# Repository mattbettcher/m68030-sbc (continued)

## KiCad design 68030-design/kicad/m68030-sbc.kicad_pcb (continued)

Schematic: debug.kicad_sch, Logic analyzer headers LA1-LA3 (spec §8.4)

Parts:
J11: LA1 A31-A0; PinHeader_2x20_P2.54mm_Vertical; MPN Samtec TSW-120-07-G-D
J12: LA2 D31-D0; PinHeader_2x20_P2.54mm_Vertical; MPN Samtec TSW-120-07-G-D
J13: LA3 control; PinHeader_2x20_P2.54mm_Vertical; MPN Samtec TSW-120-07-G-D
TP1101: LED_n; TestPoint_Pad_D1.5mm
TP1102: HALT_LED_n; TestPoint_Pad_D1.5mm

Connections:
/A0: J11.39; also elsewhere on the board
/A1: J11.38; also elsewhere on the board
/A2: J11.37; also elsewhere on the board
/A3: J11.36; also elsewhere on the board
/A4: J11.34; also elsewhere on the board
/A5: J11.33; also elsewhere on the board
/A6: J11.32; also elsewhere on the board
/A7: J11.31; also elsewhere on the board
/A8: J11.29; also elsewhere on the board
/A9: J11.28; also elsewhere on the board
/A10: J11.27; also elsewhere on the board
/A11: J11.26; also elsewhere on the board
/A12: J11.24; also elsewhere on the board
/A13: J11.23; also elsewhere on the board
/A14: J11.22; also elsewhere on the board
/A15: J11.21; also elsewhere on the board
/A16: J11.19; also elsewhere on the board
/A17: J11.18; also elsewhere on the board
/A18: J11.17; also elsewhere on the board
/A19: J11.16; also elsewhere on the board
/A20: J11.14; also elsewhere on the board
/A21: J11.13; also elsewhere on the board
/A22: J11.12; also elsewhere on the board
/A23: J11.11; also elsewhere on the board
/A24: J11.9; also elsewhere on the board
/A25: J11.8; also elsewhere on the board
/A26: J11.7; also elsewhere on the board
/A27: J11.6; also elsewhere on the board
/A28: J11.4; also elsewhere on the board
/A29: J11.3; also elsewhere on the board
/A30: J11.2; also elsewhere on the board
/A31: J11.1; also elsewhere on the board
/AS_n: J13.2; also elsewhere on the board
/AVEC_n: J13.23; also elsewhere on the board
/BERR_n: J13.14; also elsewhere on the board
/CBACK_n: J13.22; also elsewhere on the board
/CBREQ_n: J13.21; also elsewhere on the board
/CIIN_n: J13.19; also elsewhere on the board
/CLK_LA: J13.1; also elsewhere on the board
/D0: J12.39; also elsewhere on the board
/D1: J12.38; also elsewhere on the board
/D2: J12.37; also elsewhere on the board
/D3: J12.36; also elsewhere on the board
/D4: J12.34; also elsewhere on the board
/D5: J12.33; also elsewhere on the board
/D6: J12.32; also elsewhere on the board
/D7: J12.31; also elsewhere on the board
/D8: J12.29; also elsewhere on the board
/D9: J12.28; also elsewhere on the board
/D10: J12.27; also elsewhere on the board
/D11: J12.26; also elsewhere on the board
/D12: J12.24; also elsewhere on the board
/D13: J12.23; also elsewhere on the board
/D14: J12.22; also elsewhere on the board
/D15: J12.21; also elsewhere on the board
/D16: J12.19; also elsewhere on the board
/D17: J12.18; also elsewhere on the board
/D18: J12.17; also elsewhere on the board
/D19: J12.16; also elsewhere on the board
/D20: J12.14; also elsewhere on the board
/D21: J12.13; also elsewhere on the board
/D22: J12.12; also elsewhere on the board
/D23: J12.11; also elsewhere on the board
/D24: J12.9; also elsewhere on the board
/D25: J12.8; also elsewhere on the board
/D26: J12.7; also elsewhere on the board
/D27: J12.6; also elsewhere on the board
/D28: J12.4; also elsewhere on the board
/D29: J12.3; also elsewhere on the board
/D30: J12.2; also elsewhere on the board
/D31: J12.1; also elsewhere on the board
/DRAM_SEL_n: J13.36; also elsewhere on the board
/DSACK0_n: J13.13; also elsewhere on the board
/DSACK1_n: J13.12; also elsewhere on the board
/DS_n: J13.3; also elsewhere on the board
/ECS_n: J13.32; also elsewhere on the board
/FC0: J13.11; also elsewhere on the board
/FC1: J13.9; also elsewhere on the board
/FC2: J13.8; also elsewhere on the board
/HALT_LED_n: TP1102.1; also elsewhere on the board
/HALT_n: J13.16; also elsewhere on the board
/IPEND_n: J13.28; also elsewhere on the board
/IPL0_n: J13.27; also elsewhere on the board
/IPL1_n: J13.26; also elsewhere on the board
/IPL2_n: J13.24; also elsewhere on the board
/LED_n: TP1101.1; also elsewhere on the board
/OCS_n: J13.33; also elsewhere on the board
/REFILL_n: J13.31; also elsewhere on the board
/RESET_n: J13.17; also elsewhere on the board
/RMC_n: J13.34; also elsewhere on the board
/R_W: J13.4; also elsewhere on the board
/SIZ0: J13.7; also elsewhere on the board
/SIZ1: J13.6; also elsewhere on the board
/STATUS_n: J13.29; also elsewhere on the board
/STERM_n: J13.18; also elsewhere on the board
GND: J11.5, J11.10, J11.15, J11.20, J11.25, J11.30, J11.35, J11.40, J12.5, J12.10, J12.15, J12.20, J12.25, J12.30, J12.35, J12.40, J13.5, J13.10, J13.15, J13.20, J13.25, J13.30, J13.35, J13.40; also elsewhere on the board

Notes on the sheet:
Logic analyzer (spec §8.4). Keep the headers within about 25 mm of the CPU [EST] so the stubs stay short. Pin order on each header: signals on every pin that is not a multiple of 5; pins 5/10/15/20/25/30/35/40 are GND. LA1 is A31 down to A0. LA2 is D31 down to D0. LA3 is the §8.4 list, in that orde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

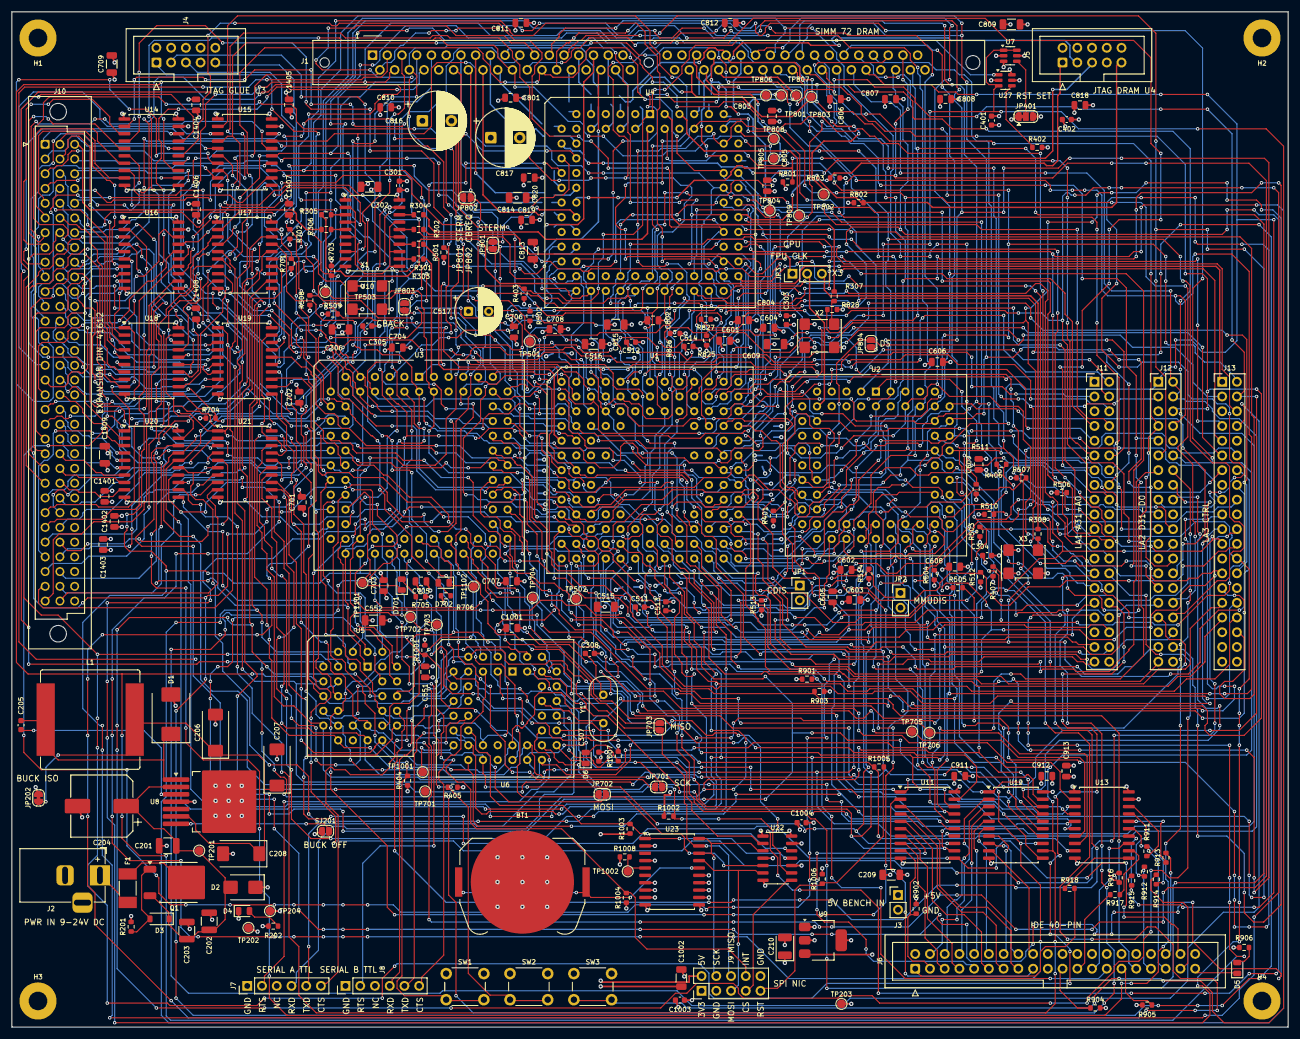
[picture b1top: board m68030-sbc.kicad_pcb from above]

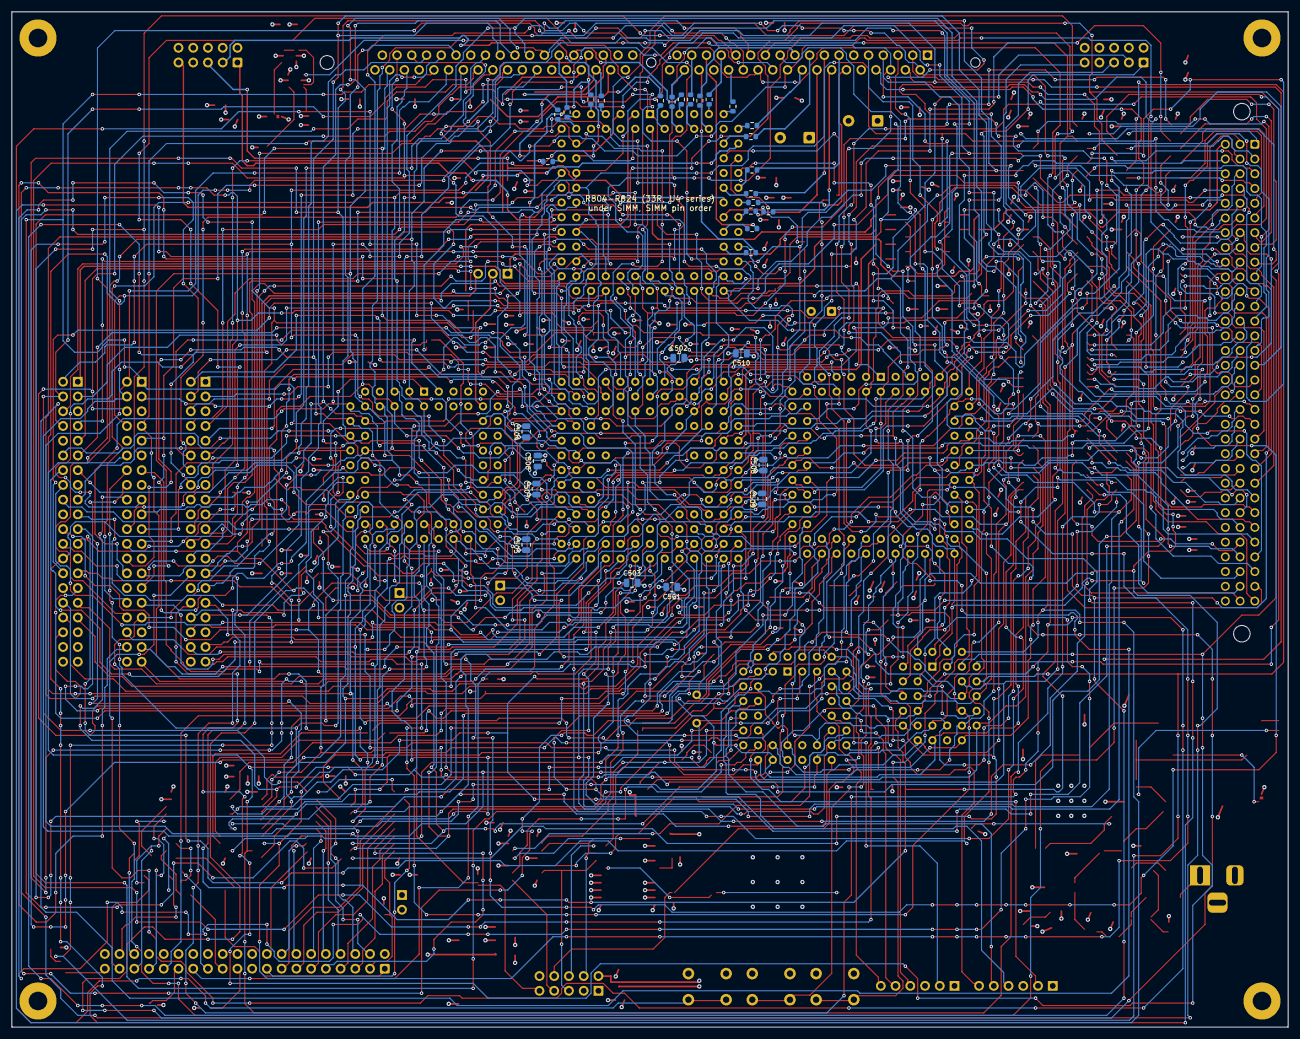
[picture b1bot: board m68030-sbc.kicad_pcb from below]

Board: 4 copper layers, 220.0 x 175.0 mm, 279 parts (31 on the bottom side), 349 nets.

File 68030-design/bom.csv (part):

ref,qty,part number,description,package/footprint suggestion,source,approx unit price (USD),notes
U1,1,MC68030RC33C,"MC68030 32-bit CPU with MMU, 33 MHz grade, run at 25 MHz","m68030-sbc:PGA128_13x13_MC68030 (derived from mackerel-68k, MIT) + 13x13 PGA-128 socket",Rochester Electronics via DigiKey (authorized),177.94,Price per Findchips 2026-09-26 (374 pcs). Avoid remarked broker parts. RC25C $171.44 / RC40C $185.31 also listed
XU1,1,PGA-128 13x13 socket (e.g. machined-pin),Socket for U1,"m68030-sbc:PGA128_13x13_MC68030 (derived from mackerel-68k, MIT)",TBD,,Verify pin grid and 0.762 mm drill vs chosen socket [VERIFY]
U2,1,MC68882FN33A (or FN25A),"MC68882 FPU, PLCC-68; must be rated >= CPU clock when on shared clock",Package_LCC:PLCC-68_THT-Socket,Brokers (FN33A); verify authenticity,,"No price found for FN25A/FN33A. In-stock EI16A ($67.29) / FN16AR2 ($47.61) / FN20A ($24, Bristol) are too slow for 25 MHz shared clock; usable only with X3/JP3 separate FPU clock"
XU2,1,PLCC-68 THT socket,Socket for U2,Package_LCC:PLCC-68_THT-Socket,TBD,,
U3,1,ATF1508AS-7JX84,"CPLD 128 macrocell, PLCC-84, 7.5 ns: glue/system controller",Package_LCC:PLCC-84_THT-Socket,Microchip Direct,12.58,Findchips 2026-09-26: 661 in stock; projected EOL 2045. Fitted: 111/128 MC (cpld/glue/glue.jed)
U4,1,ATF1508AS-7JX84,"CPLD 128 macrocell, PLCC-84: DRAM controller",Package_LCC:PLCC-84_THT-Socket,Microchip Direct,12.58,"FITTED: 80/128 MC, 55/60 I/O, reg-reg 14.0 ns (50 MHz met); JEDEC cpld/dram/dram.jed; program via J5"
"XU3,XU4",2,PLCC-84 THT socket,Sockets for U3/U4,Package_LCC:PLCC-84_THT-Socket,TBD,,
U5,1,SST39SF040-70-4C-NHE,"512K x 8 NOR flash, 70 ns, 5 V, PLCC-32 (boot ROM on D31-24)",Package_LCC:PLCC-32_THT-Socket,Microchip / distributors,2.79,Findchips 2026-09-26 listing; -70-4C-PHE (DIP-32) $4.13 at Newark
XU5,1,PLCC-32 THT socket,Socket for U5,Package_LCC:PLCC-32_THT-Socket,TBD,,
U6,1,SC26C92A1A,"DUART (SC26C92, Intel bus only), 8-byte FIFOs, PLCC-44",Package_LCC:PLCC-44_THT-Socket,Brokers only (Digi-Key/Mouser/Rochester stock 0 on 2026-10-03),11.68,Kept 2026-10-03. XR68C681 is MaxLinear OBS (PDN 2024-01-23) and Motorola bus. TL16C552A misses td2/td4 >= 80 ns on 2 WS. Pin 12 NC. Linux sccnxp sc2692 id (38.4 kbaud). SC28L92A1A fits the same socket
XU6,1,PLCC-44 THT socket,Socket for U6,Package_LCC:PLCC-44_THT-Socket,TBD,,
U7,1,TPS3702CX50DDCR,"Window supervisor, 5 V: UV 4.80 V / OV 5.20 V (+/-0.9%), SET high; open-drain UV/OV",Package_TO_SOT_SMD:SOT-23-6,DigiKey,2.82,Findchips 2026-09-26: 2837 in stock. Feeds U27 MR (spec 7.2)
U27,1,TPS3808G50DBVT,"Supervisor with delay + manual reset, 4.65 V, open-drain RESET, CT=100k to VDD -> 300 ms",Package_TO_SOT_SMD:SOT-23-6,DigiKey,2.36,Findchips 2026-09-26: DBVT 1381 in stock (DBVR 0). Output PWR_RST_n
U8,1,LM2678S-5.0/NOPB,"5 V 5 A SIMPLE SWITCHER buck, 8-40 V in",Package_TO_SOT_SMD:TO-263-7_TabPin4,DigiKey,9.26,"Findchips 2026-09-26: 466 in stock. TO-263-7 pins 1 VSW, 2 VIN, 3 CB, 4 GND/tab, 5 NC, 6 FB, 7 ON/OFF (SNVS029L). Project symbol m68030-sbc:LM2678S-5.0"
L1,1,Bourns SRP1770TA-220M,"22 uH power inductor, DCR 26.5 mOhm max, Irms 12 A, Isat 18 A (LM2678 nomograph L41 = 22 uH)",Inductor_SMD:L_Bourns_SRP1770TA_16.9x16.9mm,TBD,,SNVS029L Fig 7-3 @ 24 V / 4 A
D1,1,B540C-13-F,Schottky catch diode 40 V 5 A (VR >= 1.3 x 24 V),Diode_SMD:D_SMC,TBD,,SNVS029L step 6 / Table 7-4 class
D2,1,SMBJ28CA,"Bidirectional TVS, 28 V standoff, on VIN after Q1",Diode_SMD:D_SMB,TBD,,Clamp ~45 V at rated Ipp vs LM2678 45 V abs max [EST]
D3,1,MMSZ5242B,"12 V zener, Q1 gate-source clamp",Diode_SMD:D_SOD-123,TBD,,[VERIFY stock]
Q1,1,SUD50P04-08-GE3 (or -BE3),"P-channel MOSFET 40 V 8.1 mOhm, reverse-polarity protection",Package_TO_SOT_SMD:TO-252-2,Newark / TME,2.61,Findchips 2026-09-26: Newark 1851 pcs (-BE3) $2.61; TME 1622 pcs (-GE3). Vgs +/-20 V -> D3 clamp
R201,1,10k 0603,Q1 gate pull-down,Resistor_SMD:R_0603_1608Metric,TBD,,
F1,1,Littelfuse 0454005.MR,"Input fuse, NANO2 454 Slo-Blo SMD, 5 A, 125 V AC/DC (replaces 5x20 T5A + Schurter holder)",Fuse:Fuse_Littelfuse-NANO2-451_453,DigiKey / Newark,2.71,"Same 5 A time-lag rating as the old T5A. 50 A @125 V / 300 A @32 VDC interrupt. KiCad 451/453 land pattern = 454 datasheet pad layout (1.96x3.15 mm, 2.95 mm gap). DigiKey 5,930 stock as listed by an aggregator 2026-10-09"
J2,1,"DC barrel jack with switch pin, 2.1 or 2.5 mm, centre +",9-24 V DC input,Connector_BarrelJack:BarrelJack_Horizontal,TBD,,Symbol Connector:Barrel_Jack_Switch; pins 2+3 to GND. Verify footprint vs chosen jack [VERIFY]
J3,1,1x2 2.54 mm header (DNP),Optional bench 5 V input (cut JP202 to isolate the buck),Connector_PinHeader_2.54mm:PinHeader_1x02_P2.54mm_Vertical,TBD,,
U9,1,AMS1117-3.3,3.3 V LDO for NIC module + U22,Package_TO_SOT_SMD:SOT-223-3_TabPin2,TBD,,"C209 10 uF in, C210 22 uF solid tantalum out (AMS1117 datasheet 'Stability')"
X1,1,ECS-3951M-250-BN-TR,"25.000 MHz 5 V HCMOS XO, 7x5 mm SMD, +-50 ppm, -40..85 C",m68030-sbc:Oscillator_SMD_ECS-3951M_7.0x5.0mm_DIP14PinMap,DigiKey / Mouser (ECS authorized),,"Replaces DIP-14 can. Pad1 tri-state tied +5V (enabled >2.2 V); footprint pad numbers 1/7/8/14 map to ECS pads 1/2/3/4 so schematic is unchanged. Stock seen at several distributors; LCSC 0. Not socketed any more: to change CPU clock, rework the SMD part [VERIFY land pattern vs ECS Fig. 2]"
X2,1,ECS-3951M-500-BN-TR,"50.000 MHz 5 V HCMOS XO, 7x5 mm SMD, +-50 ppm, 55 mA max",m68030-sbc:Oscillator_SMD_ECS-3951M_7.0x5.0mm_DIP14PinMap,Mouser 520-3951M-500-BN / DigiKey XC324CT-ND,,Pad1 tri-state tied +5V. DigiKey cut-tape stock was low (53) on Octopart; Mouser 653 [VERIFY stock]
X3,1,ECS-3951M-200-BN-TR (DNP),"Optional FPU oscillator, 5 V HCMOS 7x5 SMD",m68030-sbc:Oscillator_SMD_ECS-3951M_7.0x5.0mm_DIP14PinMap,DigiKey / Mouser,,DNP. 20 MHz shown for MC68882FN20A; choose frequency to match the 68882 grade [VERIFY]
Y1,1,3.6864 MHz crystal HC-49,DUART baud clock,Crystal:Crystal_HC49-4H_Vertical,TBD,,Load caps per crystal CL
U10,1,74ACT244,"Clock fan-out buffer (8 outputs, 33 ohm series each)",Package_SO:SOIC-20W_7.5x12.8mm_P1.27mm,TBD,,
"U11,U12,U13",3,SN74ACT245DW,"IDE data (2) and control/address (1, fixed direction) buffers, SOIC-20 (DW). Was SN74ACT245N",Package_SO:SOIC-20W_7.5x12.8mm_P1.27mm,TI / Mouser 595-SN74ACT245DW,,"Same 245 pinout. Mouser listed 5,580; DigiKey 0 and one aggregator marks the DW tube obsolete - use SN74ACT245DWR (reel/cut tape) if DW is unavailable [VERIFY]"
U14-U17,4,SN74ACT244DW,"Expansion address/control buffers (A23:0, SIZ, FC, R/W, AS, DS), OE tied low",Package_SO:SOIC-20W_7.5x12.8mm_P1.27mm,TI,,
U18-U21,4,SN74ACT245DW,"Expansion data buffers D31:0 (OE=EXP_BUF_EN_n, DIR=R/W, card on the A side)",Package_SO:SOIC-20W_7.5x12.8mm_P1.27mm,TI,,
U22,1,SN74LVC125ADR,"Quad buffer, 5 V tolerant inputs, SPI 5 V to 3.3 V (SCK, MOSI, CS0, CS1). OE tied low",Package_SO:SOIC-14_3.9x8.7mm_P1.27mm,TI,,Powered from +3V3. MISO is not shifted. C1003 100 nF
U23,1,DS3234S#,SPI RTC with TCXO. VCC is +3V3 (VIH = 0.7*VCC). NC pins 2 and 7-14 to GND,Package_SO:SOIC-20W_7.5x12.8mm_P1.27mm,DigiKey,16.63,Maxim 19-5339. Both SCLK pins tied. No series diode on VBAT. C1004 100 nF. Linux rtc-ds3234 [VERIFY]
BT1,1,Keystone 3034,"CR2032 SMD coin-cell retainer (20 mm), RTC backup",Battery:BatteryHolder_Keystone_3034_1x20mm,DigiKey 36-3034-ND,0.52,"Pad 1 (+) = outer tabs, pad 2 (-) = centre pad (GND, 4 in-pad vias). DigiKey ~44k stock 2026-10"
C818-C820,3,0.1 uF X7R 0805 (DNP),Fallback mux decoupling,Capacitor_SMD:C_0805_2012Metric,TBD,,DNP
J1,1,TE Connectivity 5822021-4,"72-pin SIMM socket, vertical, 1.27 mm pitch","m68030-sbc:SIMM-72_TE-5822021-4 (new, from TE customer drawing; drill 1.02 mm, NPTH 1.63/1.63/2.41 mm)",TBD,,Replaces the Mackerel footprint (0.762 mm drill was the hole-size bug); [VERIFY] locating-hole plating per TE 114-1061
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
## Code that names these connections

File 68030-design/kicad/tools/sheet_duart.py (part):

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        u.to_label(num, net, length=17.78, hier="input")
    for num, net in (("3", "SIMM_PD1"), ("43", "SIMM_PD2"), ("42", "SIMM_PD3"), ("41", "SIMM_PD4")):
        u.to_label(num, net, length=17.78, hier="input")
    u.to_label("36", "DUART_X1", length=17.78, hier="passive")
    u.to_label("37", "DUART_X2", length=17.78, hier="passive")
    u.to_label("24", "DUART_INT_n", length=12.7, hier="output")
    u.to_power("44", "+5V", length=5.08)
    u.to_power("22", "GND", length=5.08)

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    ):
        u.to_label(num, net, length=ln)
    # 5 V side uses the hierarchical names. JP701-JP703 are open, so the CPLD pin is not on the net.
    u.to_label("31", "SPI_HW_SCK", length=22.86, hier="input")
    u.to_label("15", "SPI_HW_MOSI", length=22.86, hier="input")
    u.to_label("40", "SPI_HW_MISO", length=22.86, hier="output")

    # Drop INTRN / OP6 / OP7 below the symbol before placing parts, so they do not
    # cross the OP2-OP5 SPI stubs (a wire crossing is not a KiCad connection, but it reads as one).
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    # ----- DS3234, VCC = +3V3 (VIH = 0.7*VCC; a 5 V part would not see a valid high from the LVC125)
    rtc = sh.sym("m68030-sbc:DS3234", "U23", "DS3234S#", 355.6, 175.26, unit=1, fp=SOIC20, ds=DS_RTC,
                 fields={"MPN": "DS3234S#"}, ref_at=(340.36, 152.4), val_at=(340.36, 200.66))
    rtc.to_label("1", "SPI_CS_RTC", length=10.16)
    rtc.to_label("17", "SPI_MOSI", length=10.16)
    rtc.to_label("18", "SPI_SCK", length=10.16)
    rtc.to_label("20", "SPI_SCK", length=10.16)
    rtc.to_label("19", "SPI_HW_MISO", length=10.16)
    rtc.to_nc("3")   # 32 kHz push-pull; unused. Low if EN32kHz or BB32kHz is cleared.
    rtc.to_nc("6")   # open-drain RST, internal ~50k to VCC. No external pull-up (datasheet).
    rtc.to_power("4", "+3V3", length=5.08)
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    # straight left, clear of the CS/DIN stubs, then the pull-up sits above that run
    ex, ey = snap(ix + dx * 30.48), snap(iy + dy * 30.48)
    sh.wire((ix, iy), (ex, ey))
    sh.label("RTC_INT", ex, ey, 180)
    r = R(sh, "R1008", "10k", ex, ey - 10.16, 0,
          ref_at=(ex + 3.81, ey - 10.16), val_at=(ex + 3.81, ey - 7.62))
    top, bot = r.pin(1), r.pin(2)
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    j9.to_power("1", "+3V3", length=7.62)
    j9.to_power("2", "+5V", length=7.62)
    j9.to_power("3", "GND", length=7.62)
    j9.to_label("4", "SPI_SCK", length=10.16)
    j9.to_label("5", "SPI_MOSI", length=10.16)
    j9.to_label("6", "SPI_HW_MISO", length=10.16)
    j9.to_label("7", "SPI_CS_NIC", length=10.16)
    # INT is 3.3 V open-drain from the module. ATF1508 VIH min is 2.0 V, so no shifter.
    j9.to_label("8", "NIC_INT_n", length=12.7, hier="output")
    j9.to_label("9", "NIC_RST", length=10.16)
    j9.to_power("10", "GND", length=7.62)
    pullup_bank(sh, [("R1004", "10k", "NIC_INT_n")], 25.4, 200.66, rail="+3V3", hier="output")

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    t, b = rs.pin(1), rs.pin(2)
    upper, lower = (t, b) if t[1] < b[1] else (b, t)
    sh.wire(upper, (upper[0], upper[1] - 5.08))
    sh.hlabel("PERIPH_RST_n", "input", upper[0], upper[1] - 5.08, 90)
    sh.wire(lower, (lower[0], lower[1] + 2.54))
    sh.label("NIC_RST", lower[0] + 5.08, lower[1] + 2.54, 0)
    sh.wire((lower[0], lower[1] + 2.54), (lower[0] + 5.08, lower[1] + 2.54))
    rd = R(sh, "R1006", "2.2k", lower[0], lower[1] + 10.16, 0,
           ref_at=(lower[0] + 4.0, lower[1] + 10.16), val_at=(lower[0] + 4.0, lower[1] + 12.7))
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
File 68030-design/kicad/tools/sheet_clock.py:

from build_common import *

def osc(sh, ref, val, x, y, fp=OSC14, dnp=False, mpn=None, en_to_vcc=True):
    o = sh.sym("Oscillator:CXO_DIP14", ref, val, x, y, fp=fp, dnp=dnp, fields={"MPN": mpn} if mpn else None,
               ref_at=(x + 5.08, y - 6.35), val_at=(x + 5.08, y + 6.35))
    o.to_power("14", "+5V")
    o.to_power("7", "GND")
    if en_to_vcc:
        ex, ey = o.pin("1")
        sh.wire((ex, ey), (ex - 5.08, ey))
        sh.power("+5V", ex - 5.08, ey, 90)
    return o

def series_row(sh, ref, x, y, src_label, dst, hier=True, val="33R"):
    r = R(sh, ref, val, x, y, 90)
    a, b = r.pin(1), r.pin(2)
    sh.wire(a, (a[0] - 7.62, a[1])); sh.label(src_label, a[0] - 7.62, a[1], 180)
    sh.wire(b, (b[0] + 10.16, b[1]))
    if hier:
        sh.hlabel(dst, "output", b[0] + 10.16, b[1], 0)
    else:
        sh.label(dst, b[0] + 10.16, b[1], 0)
    return r

def build_clock(P):
    sh = P.sub("clock", "Clocks", 3)
    sh.comments = ['spec 7.1: socketed X1 (25 -> 33.333 MHz), 74ACT244 fan-out, 33R series [EST]', '68030 needs a stable, continuous clock before VCC is valid (UM 7.8)', 'Place Y1 next to U6 pins 36/37 (DUART sheet)']
    # ---------------- CPU oscillator + fan-out
    sh.text("CPU clock: X1 (socketed DIP-14 full-can) -> U10 74ACT244, one 33R series resistor per load", 30.48, 50.8, 1.5, bold=True)
    x1 = osc(sh, "X1", "25.000MHz", 68.58, 76.2, mpn="25.000 MHz 5 V CMOS full-can oscillator (socketed)")
    u10 = sh.sym("74xx:74HC244", "U10", "74ACT244", 111.76, 88.9, fp="Package_SO:SOIC-20W_7.5x12.8mm_P1.27mm",
                 ds="https://www.ti.com/lit/ds/symlink/sn74act244.pdf", fields={"MPN": "SN74ACT244DWR"},
                 ref_at=(114.3, 66.04), val_at=(114.3, 111.76))
    u10.to_power("20", "+5V"); u10.to_power("10", "GND")
    ins = ["2", "4", "6", "8", "17", "15", "13", "11"]
    pts = sorted([u10.pin(n) for n in ins], key=lambda p: p[1])
    tie_x = pts[0][0] - 5.08
    for p in pts:
        sh.wire(p, (tie_x, p[1]))
    sh.wire((tie_x, pts[0][1]), (tie_x, pts[-1][1]))
    o = x1.pin("8")
    sh.wire(o, (tie_x, o[1]))
    sh.label("OSC_CPU", o[0] + 2.54, o[1], 0)
    for n in ("1", "19"):
        p = u10.pin(n); sh.wire(p, (p[0] - 2.54, p[1]))
    p1, p2 = u10.pin("1"), u10.pin("19")
    sh.wire((p1[0] - 2.54, p1[1]), (p2[0] - 2.54, p2[1] + 2.54))
    sh.power("GND", p2[0] - 2.54, p2[1] + 2.54, 0)
    outs = [("18", "CLKB_CPU"), ("16", "CLKB_FPU"), ("14", "CLKB_GLUE"), ("12", "CLKB_DRAMC"), ("3", "CLKB_LA"), ("5", "CLKB_EXP")]
    for n, net in outs:
        u10.to_label(n, net, length=5.08)
    for n in ("7", "9"):
        u10.to_nc(n)
    sh.text("2Y2, 2Y3: spare outputs", 127.0, 99.06, 1.0)
    cap_row(sh, [("C301", "100n", C0603), ("C302", "10u", C1206)], 45.72, 104.14, 10.16)
    sh.text("X1 decoupling", 40.64, 114.3, 1.0)
    cap_row(sh, [("C303", "100n", C0603)], 134.62, 119.38, 7.62)
    sh.text("U10 decoupling", 129.54, 129.54, 1.0)
    # ---------------- series resistors
    sh.text("Series termination at the source (one load per output)", 162.56, 50.8, 1.5, bold=True)
    rows = [("R301", "CLKB_CPU", "CLK_CPU", True), ("R302", "CLKB_FPU", "CLK_FPU_CPU", False), ("R303", "CLKB_GLUE", "CLK_GLUE", True),
            ("R304", "CLKB_DRAMC", "CLK_DRAMC", True), ("R305", "CLKB_LA", "CLK_LA", True), ("R306", "CLKB_EXP", "CLK_EXP", True)]
    for i, (ref, a, b, h) in enumerate(rows):
        series_row(sh, ref, 182.88, 63.5 + i * 7.62, a, b, h)
    sh.text("CLK_CPU -> U1 CLK (E1); CLK_GLUE -> U3 pin 83 (GCLK1);\\nCLK_DRAMC -> U4 pin 2 (GCLK2); CLK_LA -> LA3; CLK_EXP -> J10", 162.56, 111.76, 1.27)
    # ---------------- FPU clock select
    sh.text("FPU clock select (spec 7.1): JP3 1-2 = CPU clock (default), 2-3 = X3", 251.46, 50.8, 1.5, bold=True)
    jp3 = sh.sym("Connector_Generic:Conn_01x03", "JP3", "FPU_CLK_SEL", 294.64, 76.2, fp=HDR3, ref_at=(297.18, 73.66), val_at=(297.18, 81.28),
                 fields={"Note": "jumper 1-2 fitted by default"})
    a, b, c = jp3.pin(1), jp3.pin(2), jp3.pin(3)
    sh.wire(a, (a[0] - 12.7, a[1])); sh.label("CLK_FPU_CPU", a[0] - 12.7, a[1], 180)
    sh.wire(b, (b[0] - 5.08, b[1])); sh.wire((b[0] - 5.08, b[1]), (b[0] - 5.08, b[1] - 10.16))
    sh.wire((b[0] - 5.08, b[1] - 10.16), (b[0] + 10.16, b[1] - 10.16))
    sh.hlabel("CLK_FPU", "output", b[0] + 10.16, b[1] - 10.16, 0)
    sh.wire(c, (c[0] - 12.7, c[1])); sh.label("CLKB_X3", c[0] - 12.7, c[1], 180)
    x3 = osc(sh, "X3", "FPU osc (DNP)", 264.16, 101.6, dnp=True, mpn="optional 5 V CMOS oscillator for a slower 68882")
    r308 = R(sh, "R308", "33R", 284.48, 101.6, 90, dnp=True)
    sh.wire(x3.pin("8"), r308.pin(1))
    b8 = r308.pin(2); sh.wire(b8, (b8[0] + 5.08, b8[1])); sh.label("CLKB_X3", b8[0] + 5.08, b8[1], 0)
    cap_row(sh, [("C304", "100n", C0603, "C", {"dnp": True})], 294.64, 119.38, 7.62)
    sh.text("X3/R308/C304 DNP unless a slower 68882 (FN16/FN20) is used", 251.46, 124.46, 1.0)
    # ---------------- DRAM clock
    sh.text("DRAM controller clock: X2 50 MHz, single load (U4 GCLK1, pin 83)", 30.48, 142.24, 1.5, bold=True)
    x2 = osc(sh, "X2", "50.000MHz", 68.58, 165.1, mpn="50.000 MHz 5 V CMOS oscillator")
    r307 = R(sh, "R307", "33R", 91.44, 165.1, 90)
    sh.wire(x2.pin("8"), r307.pin(1))
    b7 = r307.pin(2); sh.wire(b7, (b7[0] + 10.16, b7[1])); sh.hlabel("DRAM_CLK", "output", b7[0] + 10.16, b7[1], 0)
    cap_row(sh, [("C305", "100n", C0603), ("C306", "10u", C1206)], 45.72, 190.5, 10.16)
    sh.text("X2 decoupling", 40.64, 200.66, 1.0)
    # ---------------- DUART crystal
    sh.text("DUART baud clock: Y1 3.6864 MHz on U6 X1/CLK (36) and X2 (37)", 162.56, 142.24, 1.5, bold=True)
    y1 = sh.sym("Device:Crystal", "Y1", "3.6864MHz", 198.12, 162.56, 0, fp="Crystal:Crystal_HC49-4H_Vertical",
                fields={"MPN": "3.6864 MHz HC-49 (CL per chosen part)"}, ref_at=(198.12, 154.94), val_at=(198.12, 157.48), just="center")
    a, b = y1.pin(1), y1.pin(2)
    sh.wire(a, (a[0] - 17.78, a[1])); sh.hlabel("DUART_X1", "passive", a[0] - 17.78, a[1], 180)
    sh.wire(b, (b[0] + 17.78, b[1])); sh.hlabel("DUART_X2", "passive", b[0] + 17.78, b[1], 0)
    for ref, px in (("C307", a[0] - 7.62), ("C308", b[0] + 5.08)):
        c = C(sh, ref, "22p C0G", px, a[1] + 6.35, 0)
        sh.wire(c.pin(1), (px, a[1]))
        g = c.pin(2); sh.power("GND", g[0], g[1], 0)
    sh.text("C307/C308: 22 pF [EST] - size to the crystal's CL (spec 7.1).", 162.56, 180.34, 1.0)
    sh.text("Oscillator pin 1 (EN/NC on DIP-14 full cans) is tied to +5V: harmless if NC, enables the output if E/D.\\nVerify against the purchased oscillator's datasheet [VERIFY].",
            30.48, 213.36, 1.27)
    return sh

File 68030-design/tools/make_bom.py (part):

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('J9', 1, '2x5 2.54 mm header', 'SPI NIC module header (3V3, 5V, GND, SCK, MOSI, MISO, CS, INT, RST, GND)', 'Connector_PinHeader_2.54mm:PinHeader_2x05_P2.54mm_Vertical', 'TBD', '', 'W5500 or ENC28J60 module'),
('J10', 1, 'DIN 41612 type C 3x32', 'Expansion connector', 'Connector_DIN:DIN41612_C_3x32_Female_Vertical_THT', 'TBD', '', 'Mackerel uses same footprint'),
('J11-J13', 3, '2x20 2.54 mm header', 'Logic analyzer headers LA1 (A), LA2 (D), LA3 (control)', 'Connector_PinHeader_2.54mm:PinHeader_2x20_P2.54mm_Vertical', 'TBD', '', 'May be left unpopulated after bring-up'),
('JP1,JP2', 2, '1x2 header + jumper', 'CDIS_n / MMUDIS_n to GND', 'Connector_PinHeader_2.54mm:PinHeader_1x02_P2.54mm_Vertical', 'TBD', '', ''),
('JP3', 1, '1x3 header + jumper', 'FPU clock select (CPU clock / X3)', 'Connector_PinHeader_2.54mm:PinHeader_1x03_P2.54mm_Vertical', 'TBD', '', ''),
('SW1-SW3', 3, '6 mm tactile switch', 'SW1 warm reset (to glue), SW2 NMI/abort (to glue), SW3 cold reset (U27 TPS3808 MR)', 'Button_Switch_THT:SW_PUSH_6mm_H5mm', 'TBD', '', ''),
('D4-D6,D701,D702', 5, 'LED 0805', 'D4 power (R202 1k); D701 USER / D702 HALTED on the glue sheet (R705/R706 1k, U3 sinks); D5 IDE activity, D6 spare (sheets not drawn yet)', 'LED_SMD:LED_0805_2012Metric', 'TBD', '', ''),
('R701-R704', 4, '4.7k 0603', 'U3 JTAG: R701 TMS / R702 TDI pull-ups, R703 TCK pull-down; R704 EXP_INT_n pull-up (glue sheet)', 'Resistor_SMD:R_0603_1608Metric', 'TBD', '', 'JTAG values [EST]'),
('R705,R706', 2, '1k 0603', 'USER / HALTED LED series resistors (glue sheet)', 'Resistor_SMD:R_0603_1608Metric', 'TBD', '', ''),
('JP801-JP804', 4, 'Solder jumper, 2-pad, open', 'U4 pins 16/17/18/50 to STERM_n/CBREQ_n/CBACK_n/DS_n (reserved for burst / DS-qualified write; leave open)', 'Jumper:SolderJumper-2_P1.3mm_Open_RoundedPad1.0x1.5mm', 'n/a (PCB)', '', ''),
('JP701-JP703', 3, 'Solder jumper, 2-pad, open', 'U3 pins 46/48/49 to SPI_HW_SCK/MOSI/MISO (reserved CPLD SPI master; leave open)', 'Jumper:SolderJumper-2_P1.3mm_Open_RoundedPad1.0x1.5mm', 'n/a (PCB)', '', ''),
('R501-R514', 14, '1k (x9) / 10k (x5) 0603', 'CPU pull-ups: 1k DSACK0/1, STERM, CBACK, CIIN, AVEC, BERR, BR, BGACK; 10k IPL0-2, CDIS, MMUDIS', 'Resistor_SMD:R_0603_1608Metric', 'TBD', '', 'Discrete resistors on the cpu sheet'),
('R406,R407', 2, '1k 0603', 'RESET_n / HALT_n open-drain pull-ups (reset sheet)', 'Resistor_SMD:R_0603_1608Metric', 'TBD', '', ''),
('R401,R403-R405', 4, '10k 0603', 'U27 MR pull-up (TPS3702 outputs), PWR_RST_n pull-up, SW1/SW2 pull-ups', 'Resistor_SMD:R_0603_1608Metric', 'TBD', '', ''),
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('R301-R308', 8, '33 ohm 0603', 'Clock output series termination (R308 DNP)', 'Resistor_SMD:R_0603_1608Metric', 'TBD', '', 'Value [EST]; tune on scope'),
('R804-R824', 21, '33 ohm 0603', 'SIMM series termination at U4: MA0-11, RAS0-3, CAS0-3, WE (spec 5.8)', 'Resistor_SMD:R_0603_1608Metric', 'TBD', '', 'Value [EST]; tune on scope'),
('R801-R803', 3, '4.7k 0603', 'U4 JTAG: R801 TMS / R802 TDI pull-ups, R803 TCK pull-down', 'Resistor_SMD:R_0603_1608Metric', 'TBD', '', 'JTAG values [EST]'),
('R825-R828', 4, '10k 0603', 'SIMM PD1-PD4 pull-ups (to DUART IP3-IP6)', 'Resistor_SMD:R_0603_1608Metric', 'TBD', '', ''),
('R-misc', 14, '10k / 4.7k / 2.2k / 3.3k 0603', 'INTRN pull-up (4.7k), IDE INTRQ pull-down, IORDY pull-up, NIC RST divider (sheets not drawn yet)', 'Resistor_SMD:R_0603_1608Metric', 'TBD', '', 'Quantities approximate'),
('C801-C808,C810-C812', 11, '0.1 uF X7R 0805', 'U4 decoupling (one per VCC pin) + SIMM VDD pins 10/30/59', 'Capacitor_SMD:C_0805_2012Metric', 'TBD', '', ''),
('C-decouple', 59, '0.1 uF X7R 0805', 'Decoupling: 10 on CPU (C501-C510), 8 on FPU (C601-C608), 8 on U3 (C701-C708), every other logic IC', 'Capacitor_SMD:C_0805_2012Metric', 'TBD', '', 'Quantity approximate'),
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('C209', 1, '10 uF X7R 1206', 'AMS1117 input', 'Capacitor_SMD:C_1206_3216Metric', 'TBD', '', ''),
('C210', 1, '22 uF 10 V solid tantalum, EIA-3528', 'AMS1117 output (stability)', 'Capacitor_Tantalum_SMD:CP_EIA-3528-21_Kemet-B', 'TBD', '', ''),
('C307,C308', 2, '22 pF C0G 0603', 'Y1 load capacitors', 'Capacitor_SMD:C_0603_1608Metric', 'TBD', '', 'Size to crystal CL [EST]'),
('TP', 22, 'Test point', 'TP201 VIN, TP202 +5V, TP203 +3V3, TP204 GND, TP501-503 CIOUT/DBEN/BG, TP701-706 BUS_RD/BUS_WR/ROM_CE/DUART_CS/IDE_DIOR/IDE_DIOW, TP801-802 RAS0/RAS1, TP803-806 CAS0-3, TP807 WE, TP808 MUX_SEL, TP809 U4 spare pin 81', 'TestPoint:TestPoint_Pad_D1.5mm', 'TBD', '', ''),
('H1-H4', 4, 'M3 mounting hole', 'Mounting', 'MountingHole:MountingHole_3.2mm_M3_Pad', 'n/a', '', ''),
('HS1', 1, 'PGA stick-on heatsink', 'CPU cooling (up to 2.6 W)', 'n/a', 'TBD', '', ''),
]
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
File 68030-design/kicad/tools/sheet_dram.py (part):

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        if nm in ("VCC", "GND") or n in JTAG or n in JUMPERED:
            continue
        if n == 2:
            u.to_label("2", "CLK_DRAMC", length=25.4, hier="input"); continue
        if n == 81:
            u.to_label("81", "U4_SPARE81", length=10.16); continue
        assert nm, (n, "unexpected unused pin")
        if nm in HIER_IN: u.to_label(str(n), nm, length=25.4, hier="input")
        elif nm in HIER_TRI: u.to_label(str(n), nm, length=25.4, hier="tri_state")
        elif nm in STROBES: u.to_label(str(n), "U4_" + nm, length=10.16)
        elif nm == "MUX_SEL": u.to_label(str(n), "MUX_SEL", length=10.16)
        elif nm.startswith("A") and nm[1:].isdigit(): u.to_label(str(n), nm, length=7.62)
        else: raise AssertionError((n, nm))
    for n, net in JTAG.items():
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    for s, pn in (("RAS", "~{RAS%d}"), ("CAS", "~{CAS%d}")):
        for i in range(4):
            j1.to_label(pn % i, "%s%d_n" % (s, i), length=10.16)
    j1.to_label("~{WE}", "WE_n", length=10.16)
    for i in range(1, 5):
        j1.to_label("PRD%d" % i, "SIMM_PD%d" % i, length=10.16)
    for n in (11, 35, 36, 37, 38, 46, 48, 66, 71):
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    r = R(sh, "R803", "4.7k", 76.2, 190.5, 90, ref_at=(75.565, 188.595), val_at=(76.835, 188.595), just="right")
    r.s["val_just"] = "left"
    a, b = sorted([r.pin(1), r.pin(2)])
    sh.wire(a, (a[0] - 5.08, a[1])); sh.label("U4_TCK", a[0] - 5.08, a[1], 180)
    sh.wire(b, (b[0] + 2.54, b[1])); sh.wire((b[0] + 2.54, b[1]), (b[0] + 2.54, b[1] + 2.54)); sh.power("GND", b[0] + 2.54, b[1] + 2.54, 0)
    sh.text("JTAG ISP header", 22.86, 154.94, 1.5, bold=True)
    sh.text("J5: separate header for U4 (same pinout as J4 on the glue sheet; ATDH1150USB UG Table 1).\\n"
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        m = sh.sym("74xx:74LS257", "U%d" % (801 + k), "74ACT257", mx, my, fp=SO16, dnp=True,
                   ds="https://www.onsemi.com/pdf/datasheet/mc74ac257-d.pdf", fields={"MPN": "MC74ACT257DR2G"},
                   ref_at=(mx + 2.54, my - 26.67), val_at=(mx + 2.54, my + 29.21))
        m.to_label("S", "MUX_SEL", length=7.62)
        m.to_power("OE", "GND", length=5.08)
        m.to_power("VCC", "+5V", length=2.54)
        m.to_power("GND", "GND", length=2.54)
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            "Sources, reports, JEDEC, testbench: cpld/dram/ (dram.v, dram.fit, dram.jed, timing.txt, sim/).\\n"
            "Logic after Mackerel-30 dram_controller.v (C. Maykish, MIT): 50 MHz FSM, 2-flop AS synchroniser, CBR refresh\\n"
            "every 7.5 us alternating sides, 100 us + 16 CBR power-up, CAS lanes from SIZ1/SIZ0/A1/A0, DSACK1+0 (32-bit port).\\n"
            "Pins 16/17/18/50 (STERM_n/CBREQ_n/CBACK_n/DS_n) are unused in Rev A: reached only through open solder jumpers.\\n"
            "Pin 2 (GCLK2) carries CLK_DRAMC for a future CPU-synchronous (burst) FSM; pin 81 spare -> TP809.",
            22.86, 38.1, 1.0)
    sh.text("Series resistors: 33R source termination on MA/RAS/CAS/WE. Trace Z0 ~50-60R minus the CPLD output impedance\\n"
            "(~15-25R) [EST]; SIMM input loads (Micron): MA 48/95 pF, WE 64/127 pF, RAS 32 pF, CAS 16/32 pF (1/2-sided) ->\\n"
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
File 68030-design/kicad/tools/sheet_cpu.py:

from build_common import *

def bus_side(sh, part, pins, side, net_fmt, bus_x_off=12.7, wire_len=10.16):
    """connect a column of pins to a vertical bus via labels + bus entries. side 'L' or 'R'. returns (bus_x, ymin, ymax)"""
    ys = []
    for num_or_name, net in pins:
        x, y = part.pin(num_or_name)
        d = -1 if side == "L" else 1
        ex = x + d * wire_len
        sh.wire((x, y), (ex, y))
        sh.label(net, ex, y, 0 if side == "L" else 180)
        sh.bus_entry(ex, y, d * 2.54, -2.54)
        ys.append(y - 2.54)
        bx = ex + d * 2.54
    sh.bus((bx, min(ys)), (bx, max(ys)))
    return bx, min(ys), max(ys)

def build_cpu(P):
    sh = P.sub("cpu", "CPU: MC68030 PGA-128", 5)
    sh.comments = ['Pins verified vs MC68030UM sect. 14.2 (PGA) and Mackerel-68k symbol (128/128)', 'Pull-ups per spec 8.1; RESET_n/HALT_n 1k pull-ups are on the reset sheet', 'Decoupling per MC68030UM sect. 12 (10 uF + 0.1 uF + 330 pF)']
    fpC = "m68030-sbc:PGA128_13x13_MC68030"
    ds = "https://www.nxp.com/docs/en/reference-manual/MC68030UM.pdf"
    mpn = {"MPN": "MC68030RC33C", "Socket": "PGA-128 13x13 socket (XU1)"}
    # ---------------- unit A: buses
    ua = sh.sym("m68030-sbc:MC68030", "U1", "MC68030RC33C", 88.9, 121.92, unit=1, fp=fpC, ds=ds, fields=mpn,
                ref_at=(76.2, 78.74), val_at=(76.2, 167.64))
    bx, y1, y2 = bus_side(sh, ua, [("A%d" % i, "A%d" % i) for i in range(32)], "L", None)
    sh.bus((bx, y1), (bx, 71.12), (38.1, 71.12))
    sh.hlabel("A[0..31]", "output", 38.1, 71.12, 180)
    bx, y1, y2 = bus_side(sh, ua, [("D%d" % i, "D%d" % i) for i in range(32)], "R", None)
    sh.bus((bx, y1), (bx, 71.12), (137.16, 71.12))
    sh.hlabel("D[0..31]", "bidirectional", 137.16, 71.12, 0)
    sh.text("Address bus A0-A31 (outputs)", 30.48, 60.96, 1.5, bold=True)
    sh.text("Data bus D0-D31 (bidirectional)", 106.68, 60.96, 1.5, bold=True)
    # ---------------- unit B: control
    ub = sh.sym("m68030-sbc:MC68030", "U1", "MC68030RC33C", 213.36, 121.92, unit=2, fp=fpC, ds=ds, fields=mpn,
                ref_at=(200.66, 91.44), val_at=(200.66, 154.94))
    inputs = [("CLK", "CLK_CPU"), ("~{DSACK0}", "DSACK0_n"), ("~{DSACK1}", "DSACK1_n"), ("~{STERM}", "STERM_n"),
              ("~{AVEC}", "AVEC_n"), ("~{CIIN}", "CIIN_n"), ("~{CBACK}", "CBACK_n"), ("~{BERR}", "BERR_n"),
              ("~{HALT}", "HALT_n"), ("~{IPL0}", "IPL0_n"), ("~{IPL1}", "IPL1_n"), ("~{IPL2}", "IPL2_n"),
              ("~{BR}", "BR_n"), ("~{BGACK}", "BGACK_n")]
    for pn, net in inputs:
        ub.to_label(pn, net, length=22.86, hier="input")
    ub.to_label("~{RESET}", "RESET_n", length=22.86, hier="bidirectional")
    ub.to_label("~{CDIS}", "CDIS_n", length=7.62)
    ub.to_label("~{MMUDIS}", "MMUDIS_n", length=7.62)
    outs = [("FC0", "FC0"), ("FC1", "FC1"), ("FC2", "FC2"), ("SIZ0", "SIZ0"), ("SIZ1", "SIZ1"), ("R/~{W}", "R_W"),
            ("~{AS}", "AS_n"), ("~{DS}", "DS_n"), ("~{ECS}", "ECS_n"), ("~{OCS}", "OCS_n"), ("~{RMC}", "RMC_n"),
            ("~{CBREQ}", "CBREQ_n"), ("~{IPEND}", "IPEND_n"), ("~{STATUS}", "STATUS_n"), ("~{REFILL}", "REFILL_n"),
            ("~{BG}", "BG_n")]
    for pn, net in outs:
        ub.to_label(pn, net, length=22.86, hier="output")
    ub.to_label("~{DBEN}", "DBEN_n", length=7.62)
    ub.to_label("~{CIOUT}", "CIOUT_n", length=7.62)
    sh.text("Control / status", 198.12, 83.82, 1.5, bold=True)
    # ---------------- test points for CIOUT_n / DBEN_n / BG_n
    tpy = 172.72
    for i, (ref, net) in enumerate([("TP501", "CIOUT_n"), ("TP502", "DBEN_n"), ("TP503", "BG_n")]):
        x = 203.2 + i * 17.78
        tp = sh.sym("Connector:TestPoint", ref, net.replace("_n", "#"), x, tpy, 0, fp=TP, ref_at=(x + 2.54, tpy - 5.08), val_at=(x + 2.54, tpy - 2.54))
        px, py = tp.pin(1)
        sh.wire((px, py), (px, py + 5.08))
        sh.label(net, px, py + 5.08, 270)
    sh.text("Test points (spec 8.1: CIOUT_n and DBEN_n are test-point only)", 190.5, 160.02, 1.27)
    # ---------------- pull-up bank
    sh.text("Pull-ups (spec.md 8.1)", 289.56, 35.56, 1.5, bold=True)
    pu = [("R501", "1k", "DSACK0_n"), ("R502", "1k", "DSACK1_n"), ("R503", "1k", "STERM_n"), ("R504", "1k", "CBACK_n"),
          ("R505", "1k", "CIIN_n"), ("R506", "1k", "AVEC_n"), ("R507", "1k", "BERR_n"), ("R508", "1k", "BR_n"),
          ("R509", "1k", "BGACK_n"), ("R510", "10k", "IPL0_n"), ("R511", "10k", "IPL1_n"), ("R512", "10k", "IPL2_n"),
          ("R513", "10k", "CDIS_n"), ("R514", "10k", "MMUDIS_n")]
    pullup_bank(sh, pu, 304.8, 50.8)
    sh.text("1k: DSACKx (also the 68882 holding resistors), STERM, CBACK,\\nCIIN, AVEC, BERR, BR, BGACK.  10k: IPL2..0 (blank CPLD =\\nno interrupt), CDIS, MMUDIS.  RESET_n/HALT_n: reset sheet.", 289.56, 124.46, 1.27)
    # ---------------- jumpers
    for i, (ref, net, lbl) in enumerate([("JP1", "CDIS_n", "CDIS (cache disable)"), ("JP2", "MMUDIS_n", "MMUDIS (MMU disable)")]):
        y = 147.32 + i * 15.24
        j = sh.sym("Connector_Generic:Conn_01x02", ref, lbl, 320.04, y, 0, fp=HDR2, ref_at=(322.58, y - 1.27), val_at=(322.58, y + 3.81),
                   fields={"Note": "fit jumper = pull to GND"})
        p1 = j.pin(1); p2 = j.pin(2)
        sh.wire(p1, (p1[0] - 10.16, p1[1])); sh.label(net, p1[0] - 10.16, p1[1], 180)
        sh.wire(p2, (p2[0] - 5.08, p2[1])); sh.power("GND", p2[0] - 5.08, p2[1] + 0, 0) if False else None
        g = (p2[0] - 5.08, p2[1])
        sh.wire(g, (g[0], g[1] + 2.54)); sh.power("GND", g[0], g[1] + 2.54, 0)
    sh.text("JP1/JP2 open = normal operation (Linux needs the MMU)", 289.56, 175.26, 1.27)
    # ---------------- unit C: power + decoupling
    uc = sh.sym("m68030-sbc:MC68030", "U1", "MC68030RC33C", 76.2, 228.6, unit=3, fp=fpC, ds=ds, fields=mpn,
                ref_at=(104.14, 226.06), val_at=(104.14, 231.14))
    vcc = [n for n, p in uc.allpins() if p["name"] == "VCC"]
    gnd = [n for n, p in uc.allpins() if p["name"] == "GND"]
    ncs = [n for n, p in uc.allpins() if p["name"] == "NC"]
    pts = sorted(uc.pin(n) for n in vcc)
    ry = pts[0][1] - 2.54
    for p in pts: sh.wire(p, (p[0], ry))
    sh.wire((pts[0][0] - 5.08, ry), (pts[-1][0], ry))
    sh.power("+5V", pts[0][0] - 5.08, ry, 0)
    gp = sorted(uc.pin(n) for n in gnd)
    gy = gp[0][1] + 2.54
    for p in gp: sh.wire(p, (p[0], gy))
    sh.wire((gp[0][0], gy), (gp[-1][0], gy))
    sh.power("GND", gp[0][0], gy, 0)
    for n in ncs: uc.to_nc(n)
    sh.text("NC pins D5, E12, F4, F10, K5: do not connect (UM Fig. 14-1)", 76.2, 246.38, 1.27)
    specs = [("C%d" % (501 + i), "100n", C0805) for i in range(10)] + \
            [("C%d" % (511 + i), "330p", C0603, "C", {"fields": {"Dielectric": "C0G"}}) for i in range(4)] + \
            [("C515", "10u", C1206), ("C516", "10u", C1206), ("C517", "220u", "Capacitor_THT:CP_Radial_D8.0mm_P3.50mm", "CP")]
    parts, ry2 = cap_row(sh, specs, 137.16, 228.6, 10.16)
    sh.text("CPU decoupling: 10x 100 nF (one per VCC pin, under the socket), 4x 330 pF C0G, 2x 10 uF X7R, 1x 220 uF low-ESR within 20 mm", 132.08, 213.36, 1.27)
    sh.text("HEATSINK: MC68030 dissipates up to 2.6 W (EC); theta-JA ~30 C/W (PGA, EC estimate) -> up to +78 C rise.\\nFit a stick-on PGA heatsink (HS1), mandatory for 33 MHz operation.", 132.08, 254.0, 1.5, bold=True)
    return sh
